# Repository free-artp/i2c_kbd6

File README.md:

View this project on [CADLAB.io](https://cadlab.io/node/814). 

I2C adaptor for 6 keys plastic keyboard
https://www.aliexpress.com/item/1x6-Matrix-Array-6-Key-Membrane-Switch-Keypad-Keyboard-1-6-Keys-with-LED/32740817768.html?spm=2114.13010608.0.0.mCGSfq

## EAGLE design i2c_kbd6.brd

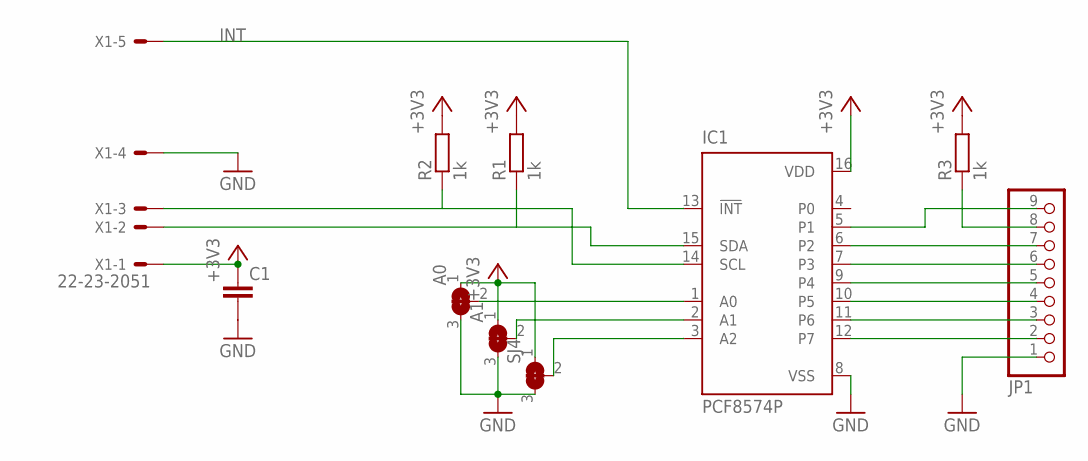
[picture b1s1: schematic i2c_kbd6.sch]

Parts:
A0, A1: SOLDERJUMPER_2WAY0805; SOLDERJUMPER_2WAY_OPEN_0805
C1: C-EUC0805; C0805
IC1: PCF8574P; DIL16
JP1: PINHD-1X9/90; 1X09/90
R1, R2, R3: 1k; R0805
SJ4: SOLDERJUMPER_2WAY0805; SOLDERJUMPER_2WAY_OPEN_0805
X1: 22-23-2051

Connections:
+3V3: A0.1, A1.1, C1.1, IC1.16 (VDD), R1.2, R2.2, R3.2, SJ4.1, X1.1
A2: IC1.3 (A2), SJ4.2
GND: A0.3, A1.3, C1.2, IC1.8 (VSS), JP1.1, SJ4.3, X1.4
INT: IC1.13 (!INT), X1.5
unnamed: IC1.15 (SDA), R1.1, X1.2
unnamed: IC1.14 (SCL), R2.1, X1.3
unnamed: A0.2, IC1.1 (A0)
unnamed: A1.2, IC1.2 (A1)
unnamed: IC1.12 (P7), JP1.2
unnamed: IC1.11 (P6), JP1.3
unnamed: IC1.10 (P5), JP1.4
unnamed: IC1.9 (P4), JP1.5
unnamed: IC1.7 (P3), JP1.6
unnamed: IC1.6 (P2), JP1.7
unnamed: IC1.5 (P1), JP1.9
unnamed: JP1.8, R3.1

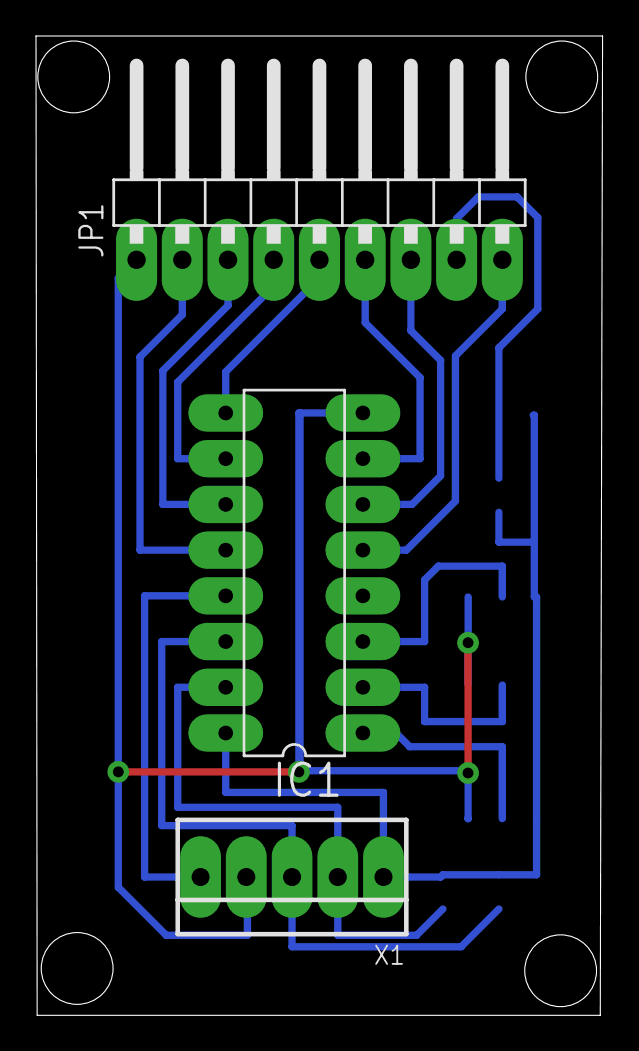
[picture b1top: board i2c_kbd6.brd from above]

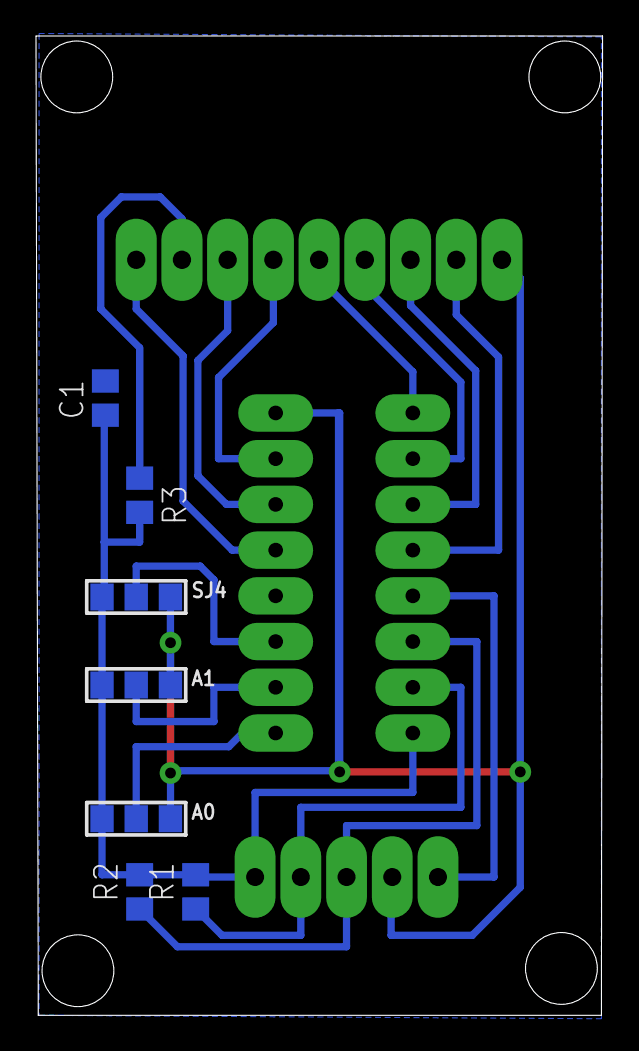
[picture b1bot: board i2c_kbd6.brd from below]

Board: 2 copper layers, 31.5 x 54.4 mm, 10 parts (7 on the bottom side), 16 nets.

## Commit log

2018-04-02 Backlink to CADLAB.io has been added.
